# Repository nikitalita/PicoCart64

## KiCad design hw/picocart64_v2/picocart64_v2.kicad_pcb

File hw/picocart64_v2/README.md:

# PicoCart64 v2.0

:exclamation: Do not produce PCBs based on this yet, boards are untested! :exclamation:

## Errata

### v1.0
- TBD

## Changelog

### v1.0

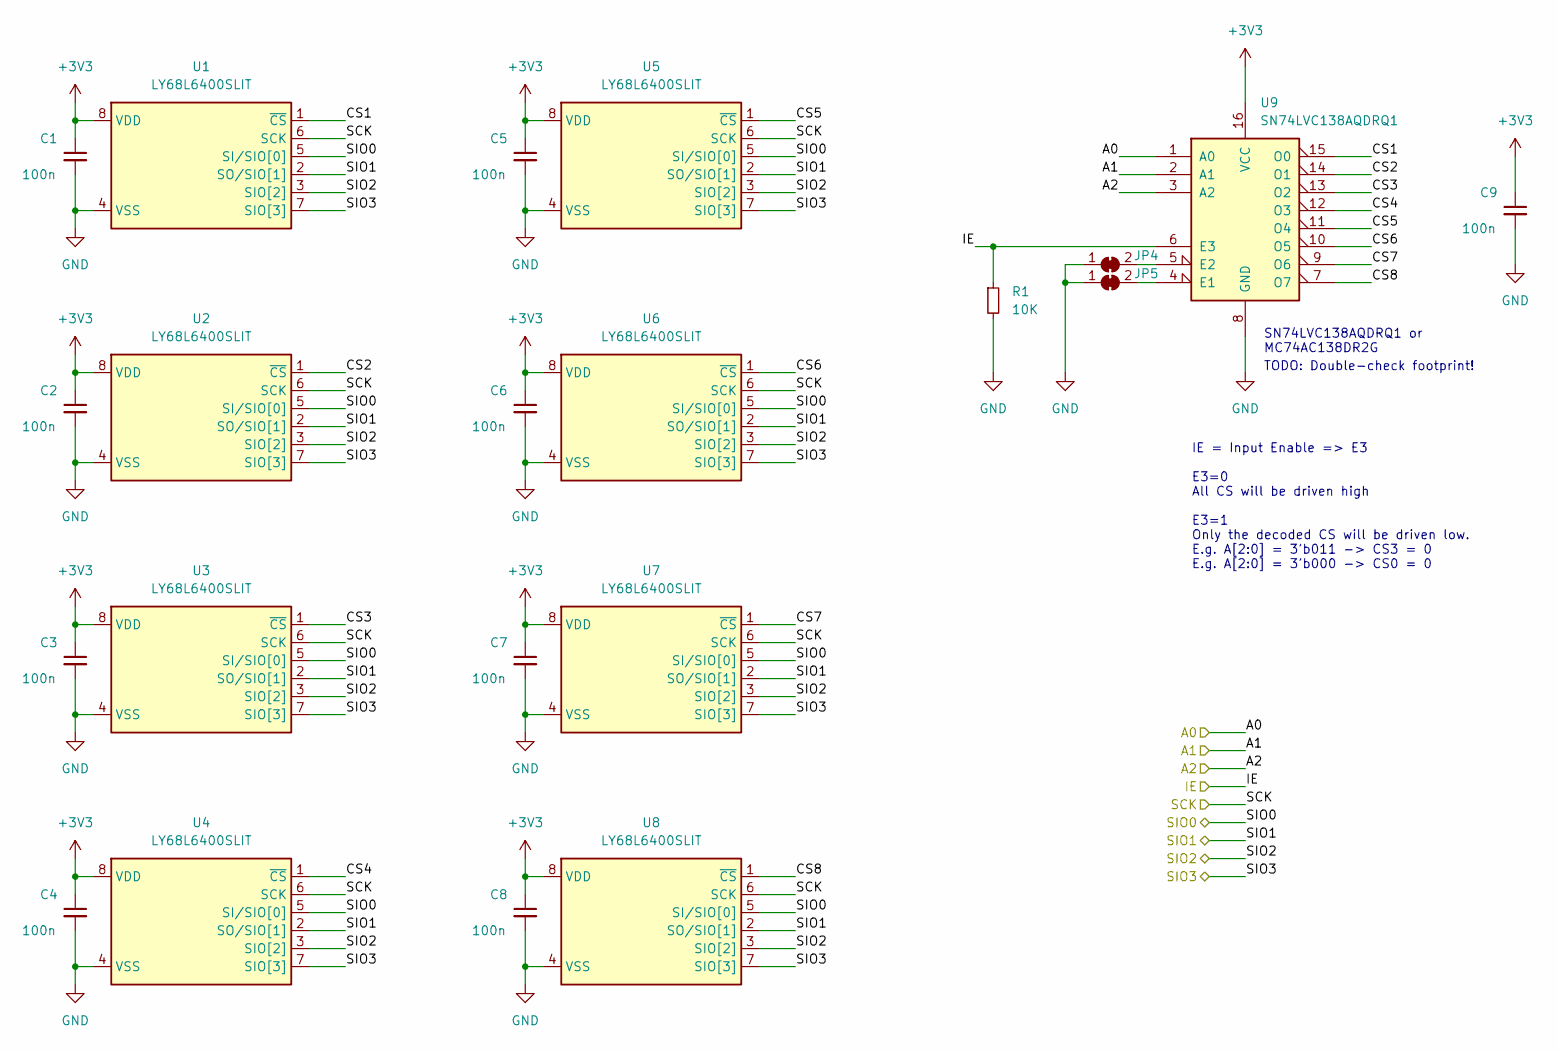
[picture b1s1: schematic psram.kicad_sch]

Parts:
C1, C2, C3, C4, C5, C6, C7, C8, C9: 100n; C_0402_1005Metric
JP4, JP5: SolderJumper_2_Bridged; SolderJumper-2_Small_Closed
R1: 10K; R_0402_1005Metric
U1, U2, U3, U4, U5, U6, U7, U8: LY68L6400SLIT; SOIC-8_5.275x5.275mm_P1.27mm
U9: SN74LVC138AQDRQ1; SOP-16_4.4x10.4mm_P1.27mm

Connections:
+3V3: C1.1, C2.1, C3.1, C4.1, C5.1, C6.1, C7.1, C8.1, C9.1, U1.8 (VDD), U2.8 (VDD), U3.8 (VDD), U4.8 (VDD), U5.8 (VDD), U6.8 (VDD), U7.8 (VDD), U8.8 (VDD), U9.16 (VCC); also elsewhere on the board
/Mainboard/DEMUX_A0: U9.1 (A0); also elsewhere on the board
/Mainboard/DEMUX_A1: U9.2 (A1); also elsewhere on the board
/Mainboard/DEMUX_A2: U9.3 (A2); also elsewhere on the board
/Mainboard/DEMUX_IE: R1.1, U9.6 (E3); also elsewhere on the board
/Mainboard/SSI_SCLK: U1.6 (SCK), U2.6 (SCK), U3.6 (SCK), U4.6 (SCK), U5.6 (SCK), U6.6 (SCK), U7.6 (SCK), U8.6 (SCK); also elsewhere on the board
/Mainboard/SSI_SD0: U1.5 (SI/SIO[0]), U2.5 (SI/SIO[0]), U3.5 (SI/SIO[0]), U4.5 (SI/SIO[0]), U5.5 (SI/SIO[0]), U6.5 (SI/SIO[0]), U7.5 (SI/SIO[0]), U8.5 (SI/SIO[0]); also elsewhere on the board
/Mainboard/SSI_SD1: U1.2 (SO/SIO[1]), U2.2 (SO/SIO[1]), U3.2 (SO/SIO[1]), U4.2 (SO/SIO[1]), U5.2 (SO/SIO[1]), U6.2 (SO/SIO[1]), U7.2 (SO/SIO[1]), U8.2 (SO/SIO[1]); also elsewhere on the board
/Mainboard/SSI_SD2: U1.3 (SIO[2]), U2.3 (SIO[2]), U3.3 (SIO[2]), U4.3 (SIO[2]), U5.3 (SIO[2]), U6.3 (SIO[2]), U7.3 (SIO[2]), U8.3 (SIO[2]); also elsewhere on the board
/Mainboard/SSI_SD3: U1.7 (SIO[3]), U2.7 (SIO[3]), U3.7 (SIO[3]), U4.7 (SIO[3]), U5.7 (SIO[3]), U6.7 (SIO[3]), U7.7 (SIO[3]), U8.7 (SIO[3]); also elsewhere on the board
/PSRAM Array/CS1: U1.1 (~CS), U9.15 (O0)
/PSRAM Array/CS2: U2.1 (~CS), U9.14 (O1)
/PSRAM Array/CS3: U3.1 (~CS), U9.13 (O2)
/PSRAM Array/CS4: U4.1 (~CS), U9.12 (O3)
/PSRAM Array/CS5: U5.1 (~CS), U9.11 (O4)
/PSRAM Array/CS6: U6.1 (~CS), U9.10 (O5)
/PSRAM Array/CS7: U7.1 (~CS), U9.9 (O6)
/PSRAM Array/CS8: U8.1 (~CS), U9.7 (O7)
GND: C1.2, C2.2, C3.2, C4.2, C5.2, C6.2, C7.2, C8.2, C9.2, JP4.1 (A), JP5.1 (A), R1.2, U1.4 (VSS), U2.4 (VSS), U3.4 (VSS), U4.4 (VSS), U5.4 (VSS), U6.4 (VSS), U7.4 (VSS), U8.4 (VSS), U9.8 (GND); also elsewhere on the board
unnamed: JP4.2 (B), U9.5 (E2)
unnamed: JP5.2 (B), U9.4 (E1)

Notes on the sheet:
TODO: Double-check footprint!
IE = Input Enable => E3 E3=0 All CS will be driven high E3=1 Only the decoded CS will be driven low. E.g. A[2:0] = 3'b011 -> CS3 = 0 E.g. A[2:0] = 3'b000 -> CS0 = 0
SN74LVC138AQDRQ1 or MC74AC138DR2G

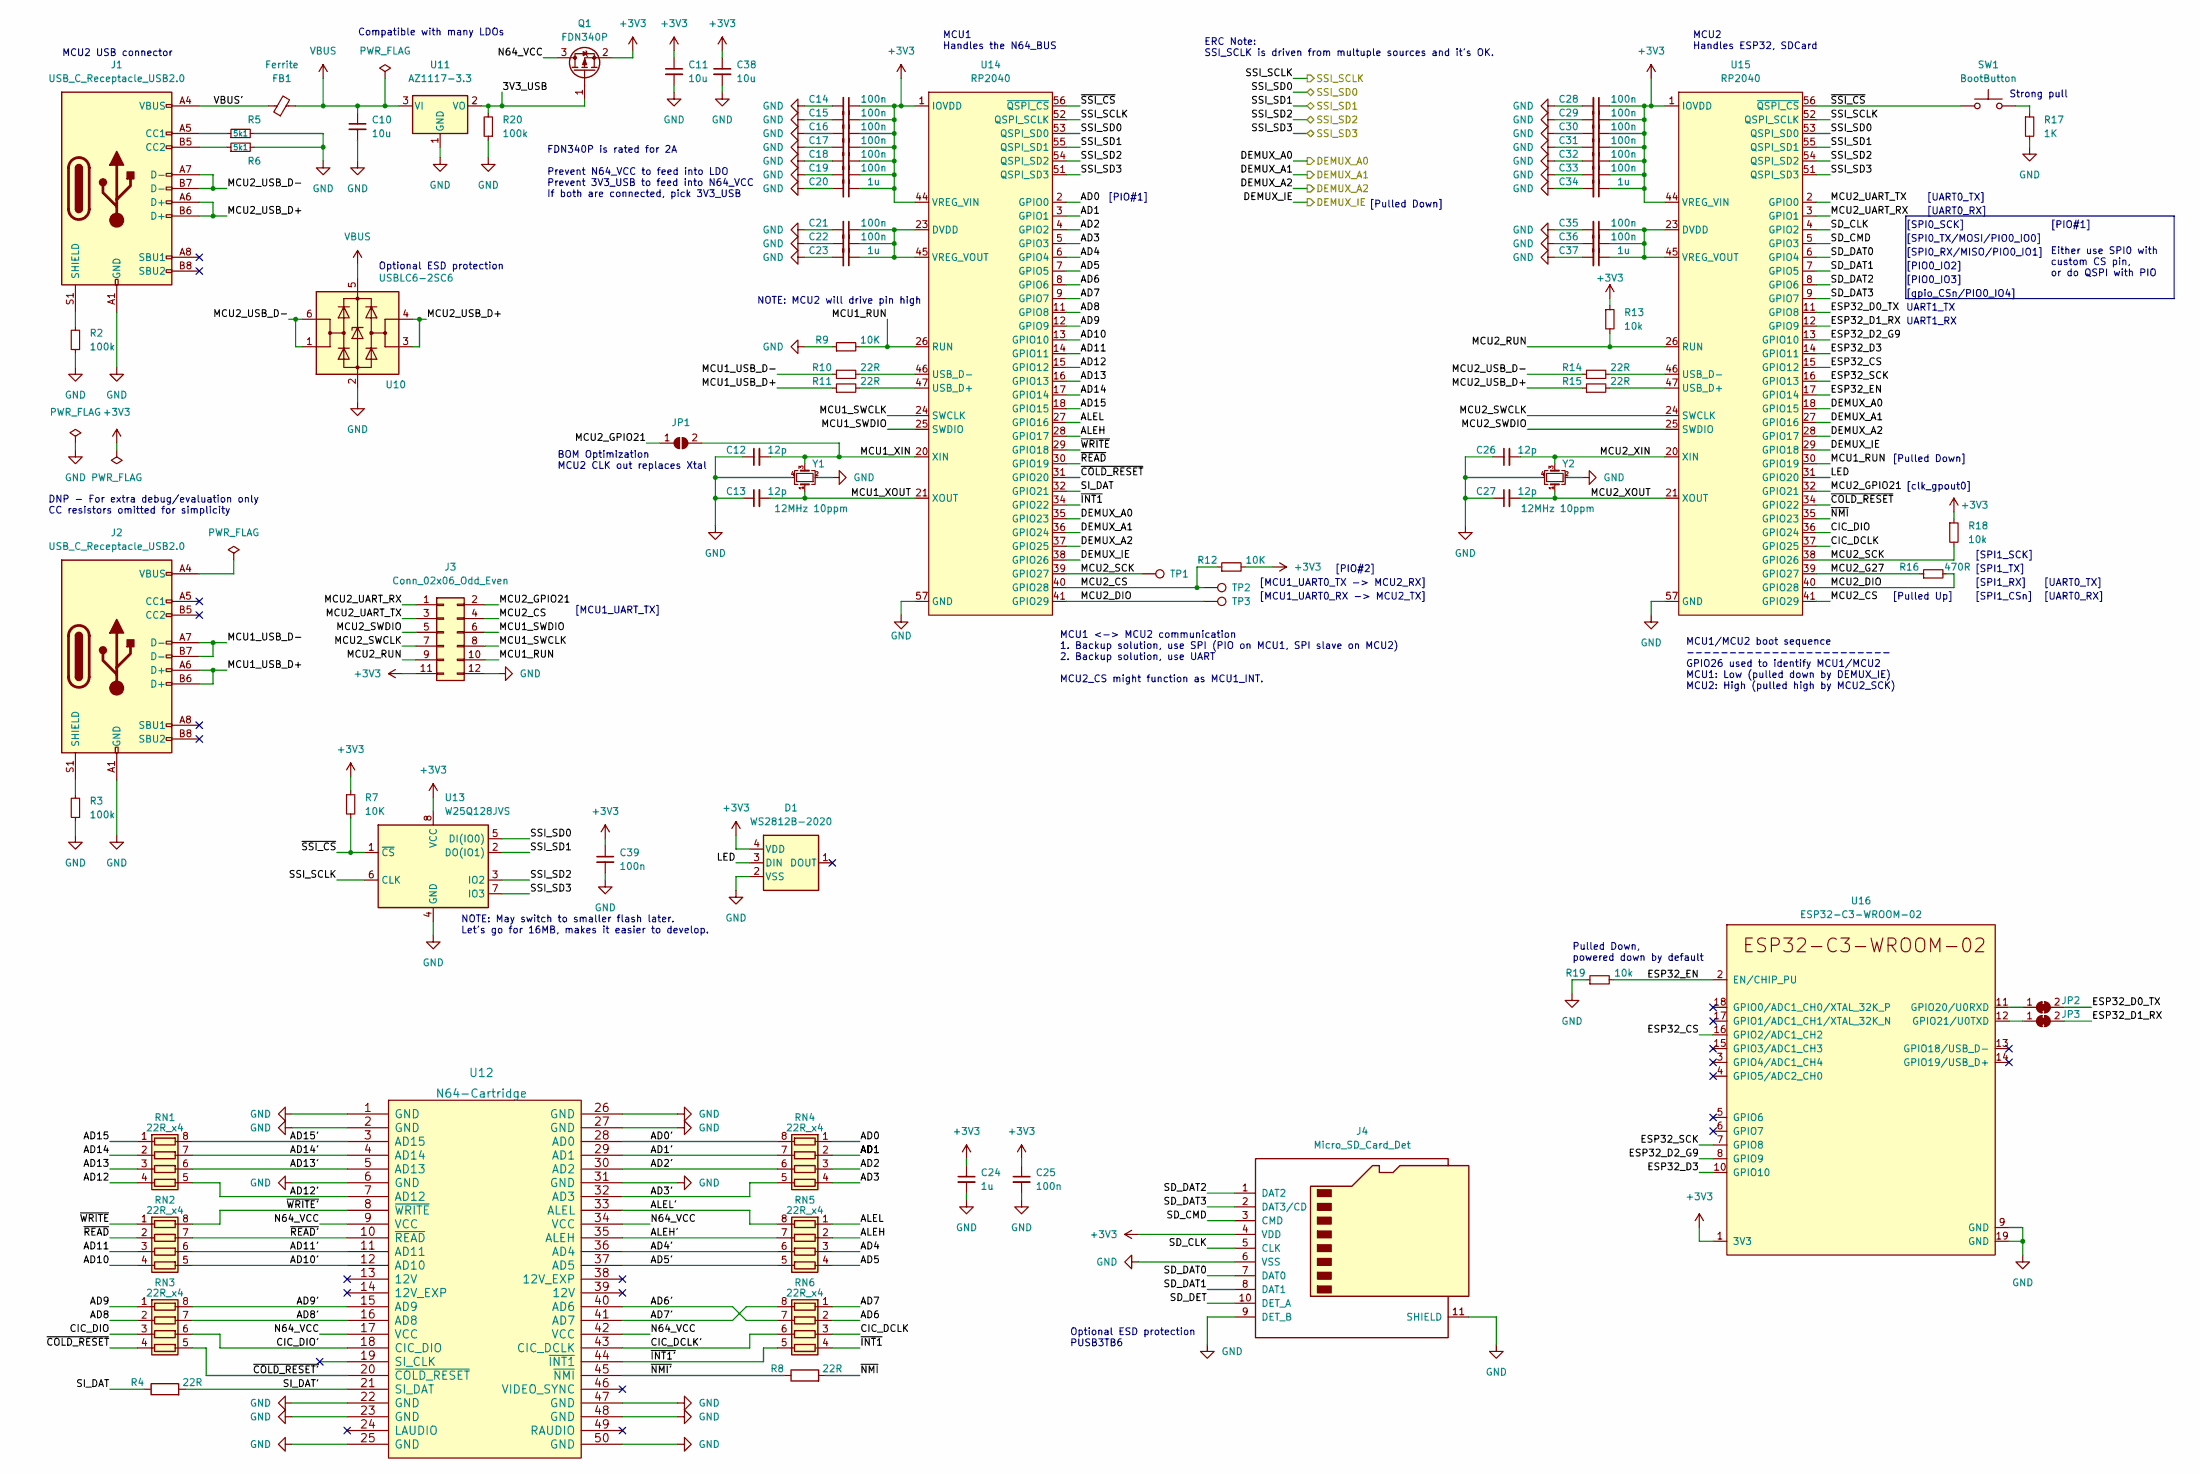
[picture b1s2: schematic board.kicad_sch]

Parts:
C10, C11, C38: 10u; C_0603_1608Metric
C12, C13, C26, C27: 12p; C_0402_1005Metric
C14, C15, C16, C17, C18, C19, C21, C22, C25, C28, C29, C30, C31, C32, C33, C35, C36, C39: 100n; C_0402_1005Metric
C20, C23, C24, C34, C37: 1u; C_0402_1005Metric
D1: WS2812B-2020
FB1: Ferrite; L_0603_1608Metric
J1, J2: USB_C_Receptacle_USB2.0; USB_C_Receptacle_GT-USB-7010
J3: Conn_02x06_Odd_Even; PinHeader_2x06_P2.54mm_Vertical_SMD
J4: Micro_SD_Card_Det; microSD_HC_Molex_104031-0811
JP1: SolderJumper_2_Open; SolderJumper-2_Small_Open
JP2, JP3: SolderJumper_2_Bridged; SolderJumper-2_Small_Closed
Q1: FDN340P; SOT-23; LCSC C347510
R2, R3, R20: 100k; R_0402_1005Metric
R4, R8, R10, R11, R14, R15: 22R; R_0402_1005Metric
R5, R6: 5k1; R_0402_1005Metric
R7, R9, R12: 10K; R_0402_1005Metric
R13, R18, R19: 10k; R_0402_1005Metric
R16: 470R; R_0402_1005Metric
R17: 1K; R_0402_1005Metric
RN1, RN2, RN3, RN4, RN5, RN6: 22R_x4; R_Array_Convex_4x0402
SW1: BootButton; SW_SPST_FSMSM
TP1: TP_MCU2_SCK; TestPoint_Pad_D1.0mm
TP2: TP_MCU2_CS; TestPoint_Pad_D1.0mm
TP3: TP_MCU2_DIO; TestPoint_Pad_D1.0mm
U10: USBLC6-2SC6; SOT-23-6; LCSC1 C15999
U11: AZ1117-3.3; SOT-223
U12: N64-Cartridge; N64-Connector
U13: W25Q128JVS; SOIC-8_5.23x5.23mm_P1.27mm
U14, U15: RP2040; QFN-56_EP_7x7_Pitch0.4mm
U16: ESP32-C3-WROOM-02
Y1, Y2: 12MHz 10ppm; Crystal_SMD_2520-4Pin_2.5x2.0mm; LCSC C521567

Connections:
+3V3: C11.1, C14.1, C15.1, C16.1, C17.1, C18.1, C19.1, C20.1, C24.1, C25.1, C28.1, C29.1, C30.1, C31.1, C32.1, C33.1, C34.1, C38.1, C39.1, D1.4 (VDD), J3.11, J4.4 (VDD), Q1.2 (S), R7.1, R12.2, R13.1, R18.1, U13.8 (VCC), U14.1 (IOVDD), U14.10 (IOVDD), U14.22 (IOVDD), U14.33 (IOVDD), U14.42 (IOVDD), U14.43 (ADC_AVDD), U14.44 (VREG_VIN), U14.48 (USB_VDD), U14.49 (IOVDD), U15.1 (IOVDD), U15.10 (IOVDD), U15.22 (IOVDD), U15.33 (IOVDD), U15.42 (IOVDD), U15.43 (ADC_AVDD), U15.44 (VREG_VIN), U15.48 (USB_VDD), U15.49 (IOVDD), U16.1 (3V3); also elsewhere on the board
/Mainboard/3V3_USB: Q1.1 (G), R20.2, U11.2 (VO)
/Mainboard/AD0: RN4.1 (R1.1), U14.2 (GPIO0)
/Mainboard/AD0': RN4.8 (R1.2), U12.28 (AD0)
/Mainboard/AD1: RN4.2 (R2.1), U14.3 (GPIO1)
/Mainboard/AD1': RN4.7 (R2.2), U12.29 (AD1)
/Mainboard/AD2: RN4.3 (R3.1), U14.4 (GPIO2)
/Mainboard/AD2': RN4.6 (R3.2), U12.30 (AD2)
/Mainboard/AD3: RN4.4 (R4.1), U14.5 (GPIO3)
/Mainboard/AD3': RN4.5 (R4.2), U12.32 (AD3)
/Mainboard/AD4: RN5.3 (R3.1), U14.6 (GPIO4)
/Mainboard/AD4': RN5.6 (R3.2), U12.36 (AD4)
/Mainboard/AD5: RN5.4 (R4.1), U14.7 (GPIO5)
/Mainboard/AD5': RN5.5 (R4.2), U12.37 (AD5)
/Mainboard/AD6: RN6.2 (R2.1), U14.8 (GPIO6)
/Mainboard/AD6': RN6.7 (R2.2), U12.40 (AD6)
/Mainboard/AD7: RN6.1 (R1.1), U14.9 (GPIO7)
/Mainboard/AD7': RN6.8 (R1.2), U12.41 (AD7)
/Mainboard/AD8: RN3.2 (R2.1), U14.11 (GPIO8)
/Mainboard/AD8': RN3.7 (R2.2), U12.16 (AD8)
/Mainboard/AD9: RN3.1 (R1.1), U14.12 (GPIO9)
/Mainboard/AD9': RN3.8 (R1.2), U12.15 (AD9)
/Mainboard/AD10: RN2.4 (R4.1), U14.13 (GPIO10)
/Mainboard/AD10': RN2.5 (R4.2), U12.12 (AD10)
/Mainboard/AD11: RN2.3 (R3.1), U14.14 (GPIO11)
/Mainboard/AD11': RN2.6 (R3.2), U12.11 (AD11)
/Mainboard/AD12: RN1.4 (R4.1), U14.15 (GPIO12)
/Mainboard/AD12': RN1.5 (R4.2), U12.7 (AD12)
/Mainboard/AD13: RN1.3 (R3.1), U14.16 (GPIO13)
/Mainboard/AD13': RN1.6 (R3.2), U12.5 (AD13)
/Mainboard/AD14: RN1.2 (R2.1), U14.17 (GPIO14)
/Mainboard/AD14': RN1.7 (R2.2), U12.4 (AD14)
/Mainboard/AD15: RN1.1 (R1.1), U14.18 (GPIO15)
/Mainboard/AD15': RN1.8 (R1.2), U12.3 (AD15)
/Mainboard/ALEH: RN5.2 (R2.1), U14.28 (GPIO17)
/Mainboard/ALEH': RN5.7 (R2.2), U12.35 (ALEH)
/Mainboard/ALEL: RN5.1 (R1.1), U14.27 (GPIO16)
/Mainboard/ALEL': RN5.8 (R1.2), U12.33 (ALEL)
/Mainboard/CIC_DCLK: RN6.3 (R3.1), U15.37 (GPIO25)
/Mainboard/CIC_DCLK': RN6.6 (R3.2), U12.43 (CIC_DCLK)
/Mainboard/CIC_DIO: RN3.3 (R3.1), U15.36 (GPIO24)
/Mainboard/CIC_DIO': RN3.6 (R3.2), U12.18 (CIC_DIO)
/Mainboard/DEMUX_A0: U14.35 (GPIO23), U15.18 (GPIO15); also elsewhere on the board
/Mainboard/DEMUX_A1: U14.36 (GPIO24), U15.27 (GPIO16); also elsewhere on the board
/Mainboard/DEMUX_A2: U14.37 (GPIO25), U15.28 (GPIO17); also elsewhere on the board
/Mainboard/DEMUX_IE: U14.38 (GPIO26), U15.29 (GPIO18); also elsewhere on the board
/Mainboard/ESP32_CS: U15.15 (GPIO12), U16.16 (GPIO2/ADC1_CH2)
/Mainboard/ESP32_D0_TX: JP2.2 (B), U15.11 (GPIO8)
/Mainboard/ESP32_D1_RX: JP3.2 (B), U15.12 (GPIO9)
/Mainboard/ESP32_D2_G9: U15.13 (GPIO10), U16.8 (GPIO9)
/Mainboard/ESP32_D3: U15.14 (GPIO11), U16.10 (GPIO10)
/Mainboard/ESP32_EN: R19.2, U15.17 (GPIO14), U16.2 (EN/CHIP_PU)
/Mainboard/ESP32_SCK: U15.16 (GPIO13), U16.7 (GPIO8)
/Mainboard/LED: D1.3 (DIN), U15.31 (GPIO20)
/Mainboard/MCU1_RUN: J3.10, R9.2, U14.26 (RUN), U15.30 (GPIO19)
/Mainboard/MCU1_SWCLK: J3.8, U14.24 (SWCLK)
/Mainboard/MCU1_SWDIO: J3.6, U14.25 (SWDIO)
/Mainboard/MCU1_USB_D+: J2.A6 (D+), J2.B6 (D+), R11.1
/Mainboard/MCU1_USB_D-: J2.A7 (D-), J2.B7 (D-), R10.1
/Mainboard/MCU1_XIN: C12.2, JP1.2 (B), U14.20 (XIN), Y1.3
/Mainboard/MCU1_XOUT: C13.2, U14.21 (XOUT), Y1.1
/Mainboard/MCU2_CS: J3.4, R12.1, TP2.1, U14.40 (GPIO28), U15.41 (GPIO29)
/Mainboard/MCU2_DIO: R16.2, TP3.1, U14.41 (GPIO29), U15.40 (GPIO28)
/Mainboard/MCU2_G27: R16.1, U15.39 (GPIO27)
/Mainboard/MCU2_GPIO21: J3.2, JP1.1 (A), U15.32 (GPIO21)
/Mainboard/MCU2_RUN: J3.9, R13.2, U15.26 (RUN)
/Mainboard/MCU2_SCK: R18.2, TP1.1, U14.39 (GPIO27), U15.38 (GPIO26)
/Mainboard/MCU2_SWCLK: J3.7, U15.24 (SWCLK)
/Mainboard/MCU2_SWDIO: J3.5, U15.25 (SWDIO)
/Mainboard/MCU2_UART_RX: J3.1, U15.3 (GPIO1)
/Mainboard/MCU2_UART_TX: J3.3, U15.2 (GPIO0)
/Mainboard/MCU2_USB_D+: J1.A6 (D+), J1.B6 (D+), R15.1, U10.3 (I/O2), U10.4 (I/O2)
/Mainboard/MCU2_USB_D-: J1.A7 (D-), J1.B7 (D-), R14.1, U10.1 (I/O1), U10.6 (I/O1)
/Mainboard/MCU2_XIN: C26.2, U15.20 (XIN), Y2.3
/Mainboard/MCU2_XOUT: C27.2, U15.21 (XOUT), Y2.1
/Mainboard/N64_VCC: Q1.3 (D), U12.9 (VCC), U12.17 (VCC), U12.34 (VCC), U12.42 (VCC)
/Mainboard/SD_CLK: J4.5 (CLK), U15.4 (GPIO2)
/Mainboard/SD_CMD: J4.3 (CMD), U15.5 (GPIO3)
/Mainboard/SD_DAT0: J4.7 (DAT0), U15.6 (GPIO4)
/Mainboard/SD_DAT1: J4.8 (DAT1), U15.7 (GPIO5)
/Mainboard/SD_DAT2: J4.1 (DAT2), U15.8 (GPIO6)
/Mainboard/SD_DAT3: J4.2 (DAT3/CD), U15.9 (GPIO7)
/Mainboard/SD_DET: J4.10 (DET_A)
/Mainboard/SI_DAT: R4.1, U14.32 (GPIO21)
/Mainboard/SI_DAT': R4.2, U12.21 (SI_DAT)
/Mainboard/SSI_SCLK: U13.6 (CLK), U14.52 (QSPI_SCLK), U15.52 (QSPI_SCLK); also elsewhere on the board
/Mainboard/SSI_SD0: U13.5 (DI(IO0)), U14.53 (QSPI_SD0), U15.53 (QSPI_SD0); also elsewhere on the board
/Mainboard/SSI_SD1: U13.2 (DO(IO1)), U14.55 (QSPI_SD1), U15.55 (QSPI_SD1); also elsewhere on the board
/Mainboard/SSI_SD2: U13.3 (IO2), U14.54 (QSPI_SD2), U15.54 (QSPI_SD2); also elsewhere on the board
/Mainboard/SSI_SD3: U13.7 (IO3), U14.51 (QSPI_SD3), U15.51 (QSPI_SD3); also elsewhere on the board
/Mainboard/VBUS': FB1.1, J1.A4 (VBUS), J1.A9 (VBUS), J1.B4 (VBUS), J1.B9 (VBUS)
/Mainboard/~COLD_RESET': RN3.5 (R4.2), U12.20 (~COLD_RESET)
/Mainboard/~COLD_RESET: RN3.4 (R4.1), U14.31 (GPIO20), U15.34 (GPIO22)
/Mainboard/~INT1': RN6.5 (R4.2), U12.44 (~INT1)
/Mainboard/~INT1: RN6.4 (R4.1), U14.34 (GPIO22)
/Mainboard/~NMI': R8.1, U12.45 (~NMI)
/Mainboard/~NMI: R8.2, U15.35 (GPIO23)
/Mainboard/~READ': RN2.7 (R2.2), U12.10 (~READ)
/Mainboard/~READ: RN2.2 (R2.1), U14.30 (GPIO19)
/Mainboard/~SSI_CS: R7.2, SW1.1, U13.1 (~CS), U14.56 (~QSPI_CS), U15.56 (~QSPI_CS)
/Mainboard/~WRITE': RN2.8 (R1.2), U12.8 (~WRITE)
/Mainboard/~WRITE: RN2.1 (R1.1), U14.29 (GPIO18)
GND: C10.2, C11.2, C12.1, C13.1, C14.2, C15.2, C16.2, C17.2, C18.2, C19.2, C20.2, C21.2, C22.2, C23.2, C24.2, C25.2, C26.1, C27.1, C28.2, C29.2, C30.2, C31.2, C32.2, C33.2, C34.2, C35.2, C36.2, C37.2, C38.2, C39.2, D1.2 (VSS), J1.A1 (GND), J1.A12 (GND), J1.B1 (GND), J1.B12 (GND), J2.A1 (GND), J2.A12 (GND), J2.B1 (GND), J2.B12 (GND), J3.12, J4.6 (VSS), J4.9 (DET_B), J4.11 (SHIELD), R2.1, R3.1, R5.2, R6.2, R9.1, R17.2, R19.1, R20.1, U10.2 (GND), U11.1 (GND), U12.1 (GND), U12.2 (GND), U12.6 (GND), U12.22 (GND), U12.23 (GND), U12.25 (GND), U12.26 (GND), U12.27 (GND), U12.31 (GND), U12.47 (GND), U12.48 (GND), U12.50 (GND), U13.4 (GND), U14.19 (TESTEN), U14.57 (GND), U15.19 (TESTEN), U15.57 (GND), U16.9 (GND), U16.19 (GND), Y1.2, Y1.4, Y2.2, Y2.4; also elsewhere on the board
unnamed: C21.1, C22.1, C23.1, U14.23 (DVDD), U14.45 (VREG_VOUT), U14.50 (DVDD)
unnamed: C35.1, C36.1, C37.1, U15.23 (DVDD), U15.45 (VREG_VOUT), U15.50 (DVDD)
unnamed: J1.A5 (CC1), R5.1
unnamed: J1.B5 (CC2), R6.1
unnamed: J1.S1 (SHIELD), R2.2
unnamed: J2.A4 (VBUS), J2.A9 (VBUS), J2.B4 (VBUS), J2.B9 (VBUS)
unnamed: J2.S1 (SHIELD), R3.2
unnamed: JP2.1 (A), U16.11 (GPIO20/U0RXD)
unnamed: JP3.1 (A), U16.12 (GPIO21/U0TXD)
unnamed: R10.2, U14.46 (USB_D-)
unnamed: R11.2, U14.47 (USB_D+)
unnamed: R14.2, U15.46 (USB_D-)
unnamed: R15.2, U15.47 (USB_D+)
unnamed: R17.1, SW1.2
VBUS: C10.1, FB1.2, U10.5 (VBUS), U11.3 (VI)

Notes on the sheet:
[UART0_TX]
[PIO0_IO2]
[Pulled Up]
[clk_gpout0]
UART1_TX
[MCU1_UART0_RX -> MCU2_TX]
NOTE: MCU2 will drive pin high
[Pulled Down]
Strong pull
[UART0_RX]
MCU2 Handles ESP32, SDCard
FDN340P is rated for 2A Prevent N64_VCC to feed into LDO Prevent 3V3_USB to feed into N64_VCC If both are connected, pick 3V3_USB
Optional ESD protection PUSB3TB6
[PIO#1]
Compatible with many LDOs
NOTE: May switch to smaller flash later. Let's go for 16MB, makes it easier to develop.
UART1_RX
BOM Optimization MCU2 CLK out replaces Xtal
[SPI1_SCK]
[SPI0_TX/MOSI/PIO0_IO0]
MCU1/MCU2 boot sequence ------------------------ GPIO26 used to identify MCU1/MCU2 MCU1: Low (pulled down by DEMUX_IE) MCU2: High (pulled high by MCU2_SCK)
[SPI0_SCK]
Either use SPI0 with custom CS pin, or do QSPI with PIO
[MCU1_UART_TX]
[SPI1_TX]
[MCU1_UART0_TX -> MCU2_RX]
[SPI1_RX]
ERC Note: SSI_SCLK is driven from multuple sources and it's OK.
MCU2 USB connector
[PIO0_IO3]
[PIO#2]
Optional ESD protection
MCU1 <-> MCU2 communication 1. Backup solution, use SPI (PIO on MCU1, SPI slave on MCU2) 2. Backup solution, use UART MCU2_CS might function as MCU1_INT.
[SPI0_RX/MISO/PIO0_IO1]
Pulled Down, powered down by default
DNP - For extra debug/evaluation only CC resistors omitted for simplicity
MCU1 Handles the N64_BUS
[gpio_CSn/PIO0_IO4]
[SPI1_CSn]

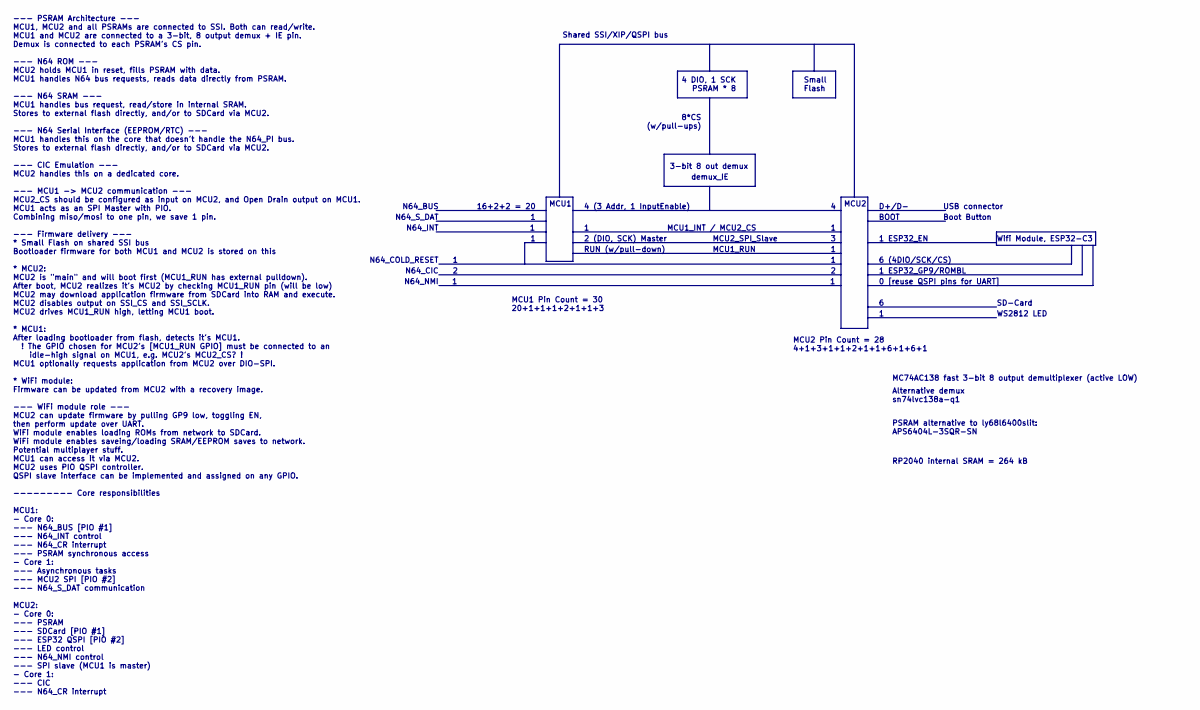
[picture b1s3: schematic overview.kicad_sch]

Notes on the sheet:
MCU1_RUN
Alternative demux sn74lvc138a-q1
4 DIO, 1 SCK PSRAM * 8
16+2+2 = 20
1 ESP32_EN
0 [reuse QSPI pins for UART]
PSRAM alternative to ly68l6400slit: APS6404L-3SQR-SN
1 ESP32_GP9/ROMBL
MCU1 Pin Count = 30 20+1+1+1+2+1+1+3
2 (DIO, SCK) Master
Shared SSI/XIP/QSPI bus
Wifi Module, ESP32-C3
Boot Button
N64_COLD_RESET
WS2812 LED
BOOT
N64_NMI
MCU2
SD-Card
USB connector
3-bit 8 out demux
RP2040 internal SRAM = 264 kB
8*CS (w/pull-ups)
N64_BUS
Small Flash
RUN (w/pull-down)
demux_IE
--- PSRAM Architecture --- MCU1, MCU2 and all PSRAMs are connected to SSI. Both can read/write. MCU1 and MCU2 are connected to a 3-bit, 8 output demux + IE pin. Demux is connected to each PSRAM's CS pin. --- N64 ROM --- MCU2 holds MCU1 in reset, fills PSRAM with data. MCU1 handles N64 bus requests,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
D+/D-
N64_INT
MCU2 Pin Count = 28 4+1+3+1+1+2+1+1+6+1+6+1
MC74AC138 fast 3-bit 8 output demultiplexer (active LOW)
MCU2_SPI_Slave
MCU1
MCU1_INT / MCU2_CS
6 (4DIO/SCK/CS)
4 (3 Addr, 1 InputEnable)
N64_S_DAT
N64_CIC

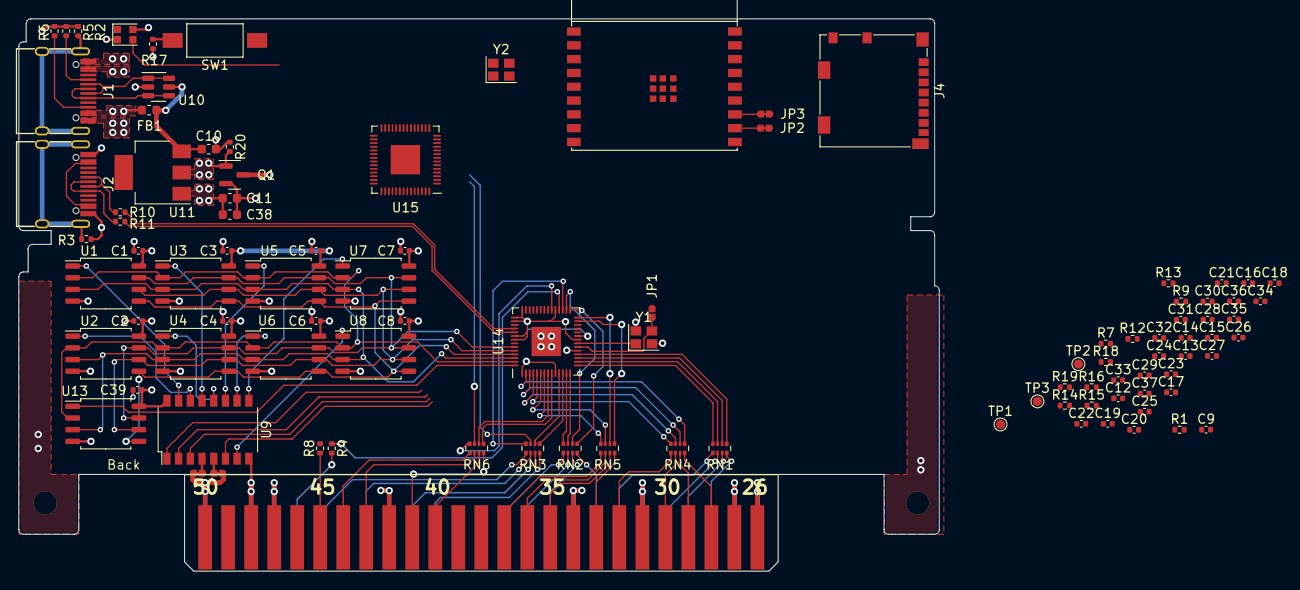
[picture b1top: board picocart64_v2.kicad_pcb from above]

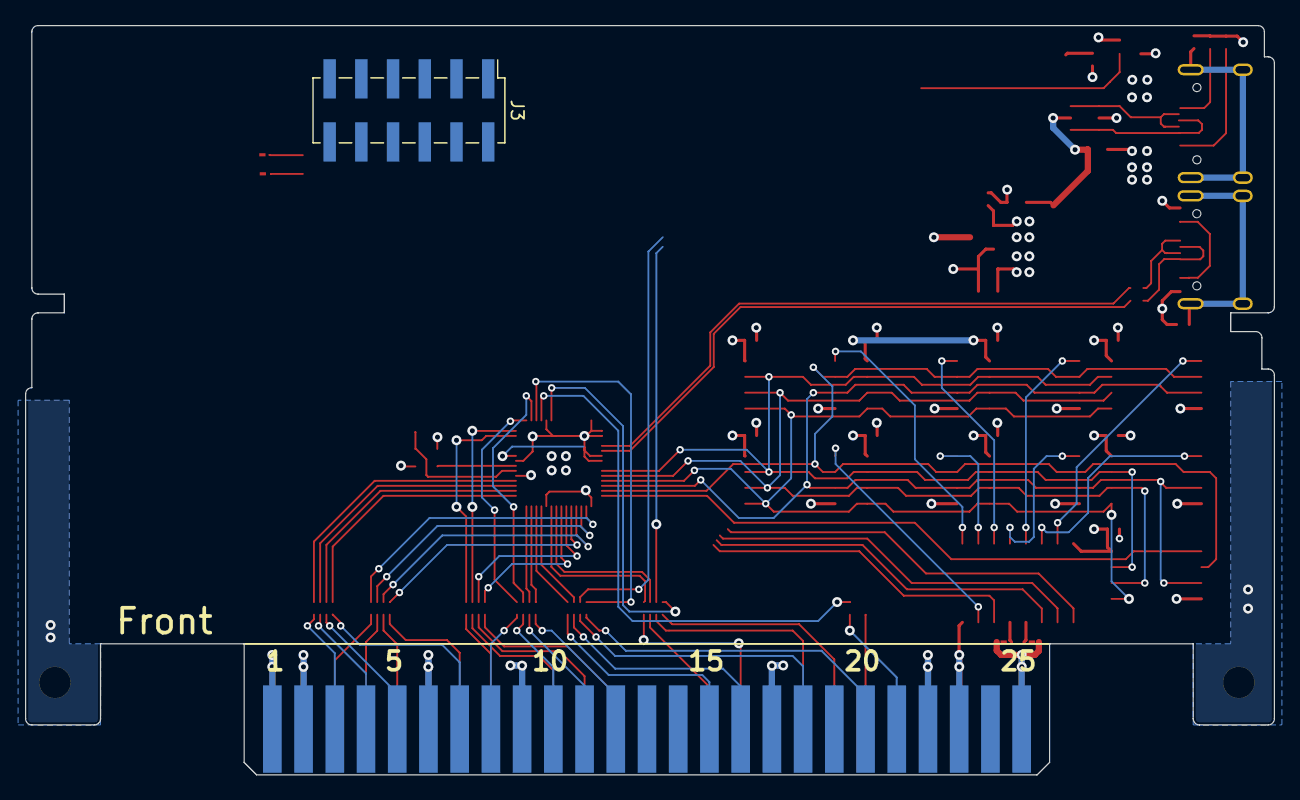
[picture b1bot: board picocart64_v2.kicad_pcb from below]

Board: 4 copper layers, 100.0 x 60.0 mm, 99 parts (2 on the bottom side), 127 nets.

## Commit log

2022-07-17 hw: Initialize picocart64_v2 project
2022-07-17 hw: v2 WIP
2022-08-03 Break out sheets
2022-08-03 Add overview
2022-08-04 Documented and figured out some stuff
2022-08-04 Update text
2022-08-09 hw: v2 Finalize schematic
2022-08-11 hw: Routing progress
2022-08-11 hw: More routing progress
